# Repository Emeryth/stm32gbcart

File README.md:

# STM32 GameBoy Cartridge

A GameBoy flashcart based on an STM32F405, with USB, battery backup and external FRAM.

Based on cartridge footprint by Gekkio [https://github.com/Gekkio/gb-hardware](https://github.com/Gekkio/gb-hardware).

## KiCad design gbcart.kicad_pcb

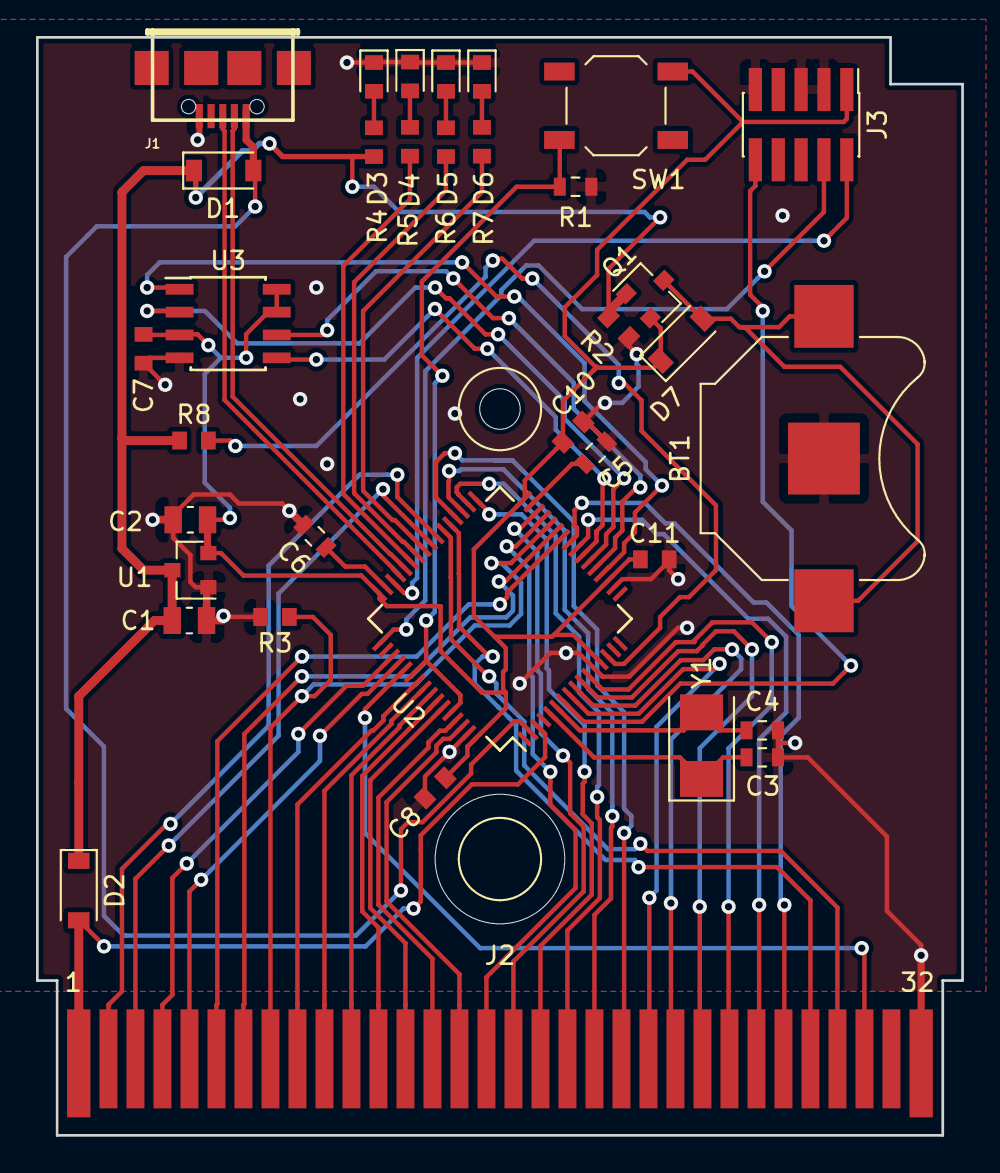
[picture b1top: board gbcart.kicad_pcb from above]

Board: 2 copper layers, 51.4 x 61.0 mm, 37 parts (0 on the bottom side), 57 nets.

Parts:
BT1: Battery_Cell; BatteryHolder_Keystone_3000_1x12mm
C1, C2: 1u; C_0805_2012Metric
C3, C4: 15p; C_0603_1608Metric
C5, C6: 2.2u; C_0603_1608Metric
C7, C8, C10, C11: 100n; C_0603_1608Metric
D1, D2, D7: D_Schottky; D_SOD-123
D3, D4, D5, D6: LED; LED_0603_1608Metric
J1: USB_B_Micro; conn_usb_B_micro_smd-2
J2: Conn_GameBoy_Cartridge; GameBoy_Cartridge
J3: Conn_ARM_JTAG_SWD_10; PinHeader_2x05_P1.27mm_Vertical_SMD
MK1, MK2: Mounting_Hole; 1pin
Q1: Q_PMOS_GSD; SOT-23
R1, R3, R8: 10k; R_0603_1608Metric
R2: 100k; R_0603_1608Metric
R4, R5, R6, R7: 470; R_0603_1608Metric
SW1: SW_Push; SW_SPST_TL3342
U1: MCP1700-1202E_SOT23; SOT-23
U2: STM32F405RGTx; LQFP-64_10x10mm_P0.5mm
U3: FM25V10; SOIC-8_3.9x4.9mm_P1.27mm
Y1: 8M; Crystal_SMD_5032-2Pin_5.0x3.2mm

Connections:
+5V: C1.1, D1.1, D2.1, Q1.1, R2.1, R4.2, R8.1, U1.3
/A0: J2.6, U2.26
/A1: J2.7, U2.27
/A2: J2.8, R3.1, U2.28
/A3: J2.9, U2.55
/A4: J2.10, U2.56
/A5: J2.11, U2.57
/A6: J2.12, U2.58
/A7: J2.13, U2.59
/A8: J2.14, U2.61
/A9: J2.15, U2.62
/A10: J2.16, U2.29
/A11: J2.17, U2.30
/A12: J2.18, U2.33
/A13: J2.19, U2.34
/A14: J2.20, U2.35
/A15: J2.21, U2.36
/BOOT0: R1.1, SW1.2, U2.54, U2.60
/CLK: J2.2, U2.39
/CS: J2.5, U2.52
/D0: J2.22, U2.8
/D1: J2.23, U2.9
/D2: J2.24, U2.10
/D3: J2.25, U2.11
/D4: J2.26, U2.24
/D5: J2.27, U2.25
/D6: J2.28, U2.37
/D7: J2.29, U2.38
/D_N: J1.2, U2.44
/D_P: J1.3, U2.45
/FRAM_CS: U2.20, U3.1
/FRAM_MISO: U2.22, U3.2
/FRAM_MOSI: U2.23, U3.5
/FRAM_SCK: U2.21, U3.6
/LED1: R5.2, U2.43
/LED2: R6.2, U2.42
/LED3: R7.2, U2.41
/RD: J2.4, U2.51
/RES: J2.30, U2.53
/RESET: J3.10, U2.7
/SWCLK: J3.4, U2.49
/SWDIO: J3.2, U2.46
/VBUS: D1.2, J1.1, U2.2
/VGB: D2.2, J2.1, U2.3
/WR: J2.3, U2.40
GND: BT1.2, C1.2, C2.2, C3.2, C4.1, C5.2, C6.2, C7.1, C8.2, C10.2, C11.2, D3.1, D4.1, D5.1, D6.1, J1.5, J2.32, J3.3, J3.5, J3.9, R1.2, R2.2, R3.2, U1.1, U2.12, U2.18, U2.63, U3.4
unnamed: BT1.1, D7.2, Q1.3
unnamed: C3.1, U2.5, Y1.1
unnamed: C4.2, U2.6, Y1.2
unnamed: C5.1, U2.31
unnamed: C6.1, U2.47
unnamed: D3.2, R4.1
unnamed: D4.2, R5.1
unnamed: D5.2, R6.1
unnamed: D6.2, R7.1
unnamed: R8.2, U2.14
VCC: C2.1, C7.2, C8.1, C10.1, C11.1, D7.1, J3.1, Q1.2, SW1.1, U1.2, U2.13, U2.19, U2.32, U2.48, U2.64, U3.3, U3.7, U3.8

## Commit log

2019-12-13 Initial commit. Sent to the fab.
2019-12-13 Add readme and license.
